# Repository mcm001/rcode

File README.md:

# rcode
stuff that doesn't belong anywhere else

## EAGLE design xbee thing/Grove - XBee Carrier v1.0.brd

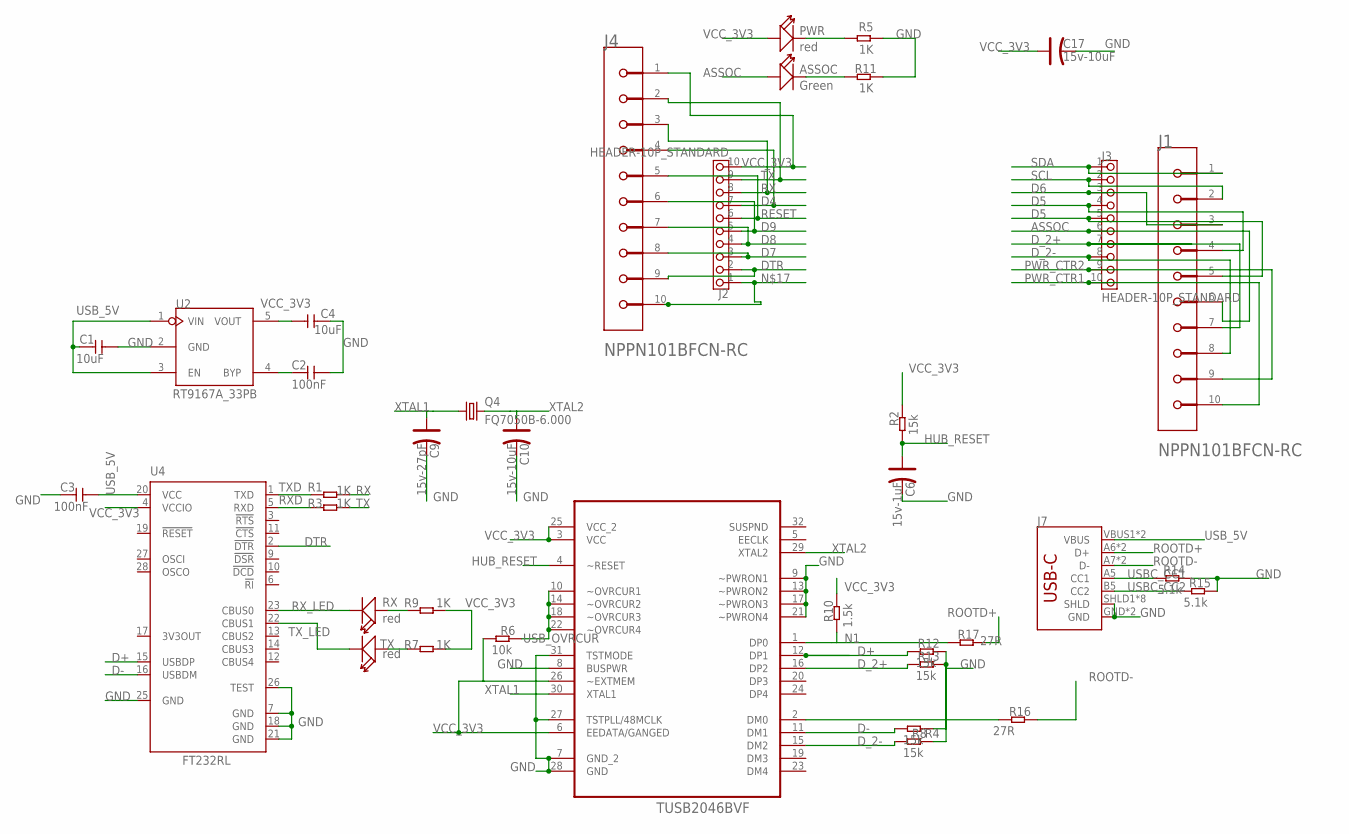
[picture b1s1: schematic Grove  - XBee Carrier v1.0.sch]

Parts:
ASSOC: Green; D0603
C1, C4: 10uF; 0805
C2, C3: 100nF; 0603
C6: 15v-1uF; AVX-A
C9: 15v-27pF; AVX-A
C10, C17: 15v-10uF; AVX-A
J1, J4: SULLINS_NPPN101BFCN-RCSULLINS_NPPN101BFCN-RC_0_0; SULLINS_NPPN101BFCN-RC_0
J2, J3: HEADER-10P_STANDARD; 2.54_10P
J7: USB_C2-LAYER; USB-C-16P
PWR: red; D0805
Q4: FQ7050B-6.000; FQ7050B
R1, R3, R5, R7, R9, R11: 1K; 0603
R2, R4, R8, R12, R13: 15k; 0603
R6: 10k; 0603
R10: 1.5k; 0603
R14, R15: 5.1k; 0603
R16, R17: 27R; 0603
RX: red; D0603
TX: red; D0603
U1: TUSB2046BVF; QFP80P900X900X145-32N
U2: RT9167A_33PB; SOT23-5
U4: FT232RL; SSOP28

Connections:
ASSOC: ASSOC.+, J1.6, J3.6
D4: J2.7, J4.4
D5: J1.4, J1.5, J3.4, J3.5
D6: J1.3, J3.3
D7: J2.3, J4.8
D8: J2.4, J4.7
D9: J2.5, J4.6
D+: R12.2, U1.12 (DP1), U4.15 (USBDP)
D-: R4.2, U1.11 (DM1), U4.16 (USBDM)
DTR: J2.2, J4.9, U4.2 (!DTR)
D_2+: J1.7, J3.7, R13.2, U1.16 (DP2)
D_2-: J1.8, J3.8, R8.2, U1.15 (DM2)
GND: C1.2, C2.2, C3.1, C4.2, C6.-, C9.-, C10.-, C17.-, J7.GND, J7.GND2 (GND), J7.SHLD1 (SHLD), J7.SHLD2 (SHLD), J7.SHLD3 (SHLD), J7.SHLD4 (SHLD), J7.SHLD5 (SHLD), J7.SHLD6 (SHLD), J7.SHLD7 (SHLD), J7.SHLD8 (SHLD), R4.1, R5.1, R8.1, R11.1, R12.1, R13.1, R14.1, R15.1, U1.7 (GND_2), U1.8 (BUSPWR), U1.9 (~PWRON1), U1.13 (~PWRON2), U1.17 (~PWRON3), U1.21 (~PWRON4), U1.27 (TSTPLL/48MCLK), U1.28 (GND), U1.31 (TSTMODE), U2.2 (GND), U4.7 (GND), U4.18 (GND), U4.21 (GND), U4.25 (GND), U4.26 (TEST)
HUB_RESET: C6.+, R2.2, U1.4 (~RESET)
N1: R10.2, R17.2, U1.1 (DP0)
unnamed: PWR.-, R5.2
unnamed: R16.2, U1.2 (DM0)
unnamed: C2.1, U2.4 (BYP)
unnamed: ASSOC.-, R11.2
unnamed: R9.1, RX.+
unnamed: R7.1, TX.+
unnamed: J2.1, J4.10
PWR_CTR1: J1.10, J3.10
PWR_CTR2: J1.9, J3.9
RESET: J2.6, J4.5
ROOTD+: J7.A6 (D+), J7.B6 (D+), R17.1
ROOTD-: J7.A7 (D-), J7.B7 (D-), R16.1
RX: J2.8, J4.3, R1.2
RXD: R3.1, U4.5 (RXD)
RX_LED: RX.-, U4.23 (CBUS0)
SCL: J1.2, J3.2
SDA: J1.1, J3.1
TX: J2.9, J4.2, R3.2
TXD: R1.1, U4.1 (TXD)
TX_LED: TX.-, U4.22 (CBUS1)
USBC_CC1: J7.A5 (CC1), R14.2
USBC_CC2: J7.B5 (CC2), R15.2
USB_5V: C1.1, C3.2, J7.VBUS1 (VBUS), J7.VBUS2 (VBUS), U2.1 (VIN), U2.3 (EN), U4.20 (VCC)
USB_OVRCUR: R6.1, U1.10 (~OVRCUR1), U1.14 (~OVRCUR2), U1.18 (~OVRCUR3), U1.22 (~OVRCUR4)
VCC_3V3: C4.1, C17.+, J2.10, J4.1, PWR.+, R2.1, R6.2, R7.2, R9.2, R10.1, U1.3 (VCC), U1.6 (EEDATA/GANGED), U1.25 (VCC_2), U1.26 (~EXTMEM), U2.5 (VOUT), U4.4 (VCCIO)
XTAL1: C9.+, Q4.1, U1.30 (XTAL1)
XTAL2: C10.+, Q4.4 (2), U1.29 (XTAL2)

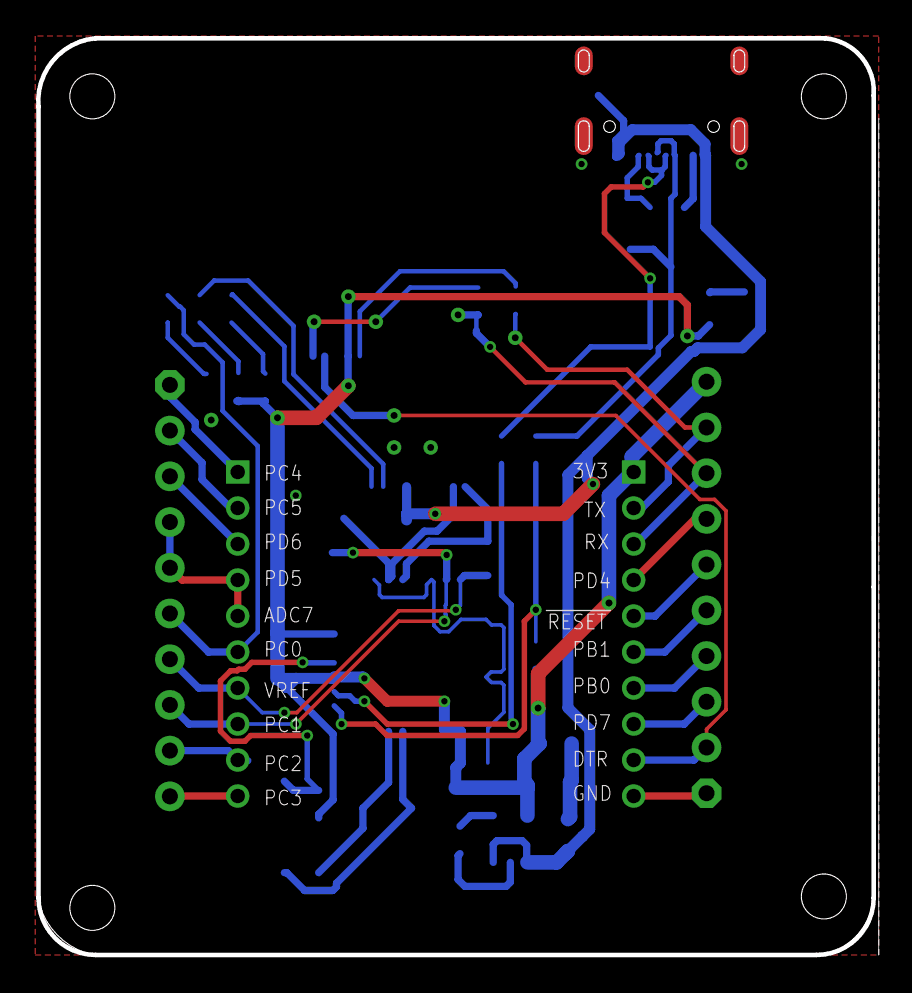
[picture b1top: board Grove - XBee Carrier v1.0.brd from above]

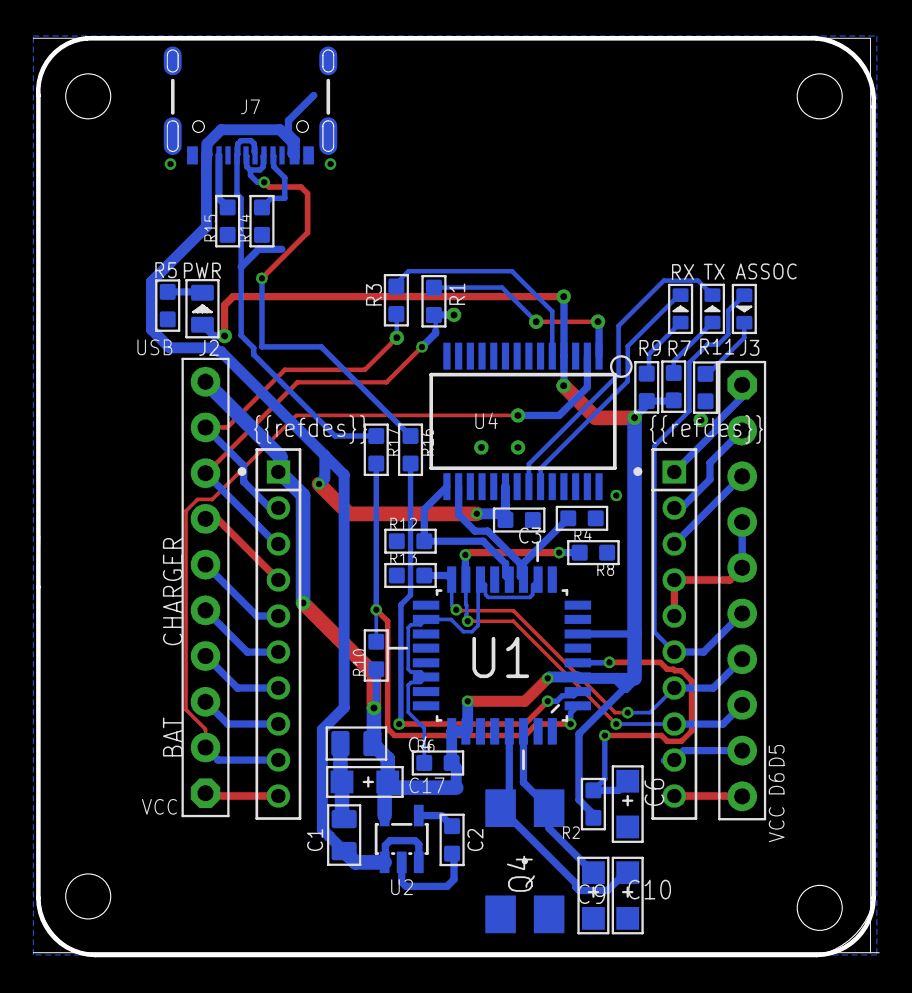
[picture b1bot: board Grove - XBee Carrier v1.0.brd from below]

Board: 2 copper layers, 46.4 x 50.9 mm, 38 parts (38 on the bottom side), 42 nets.

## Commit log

2018-11-14 added todo
2018-11-15 update todo
2018-11-25 added tensioner :D
2018-11-25 reorganization
2018-11-26 Updated to include pin retention
2018-11-26 fixed for no oled
2018-11-26 added arduino rcode
2018-11-26 fixed org
2018-11-26 banana2
2018-11-26 meme2
2018-11-26 Went and became the true fish
2018-11-27 added printer stuff
2018-11-27 meme
2018-11-27 alexisbad.jpg
2018-11-30 add endstop for z axis
2018-12-01 frc batt box stuff
2018-12-01 added nema 17 cad
2018-12-01 yeet
2018-12-01 mlem
2018-12-02 added mk3-ish
2018-12-06 update wifimd
2018-12-06 yay merge conflicts
2018-12-07 added port forwarding memes
2018-12-13 history notes yay
2018-12-22 added filament hanger hook thing
2018-12-31 owo quarter wave transforms broken
2019-01-07 reeeeee
2019-01-07 Add main grabber assem v2
2019-01-07 Moar shiv bois
2019-01-07 Add a ulna
2019-01-07 Full wrist assem
2019-01-07 Moar assem
2019-01-07 Add a yeet-o-vator
2019-01-07 More yeets for the elevator
2019-01-07 Add dimensioned drawings
2019-01-07 more yeetn't's
2019-01-24 weird
2019-01-24 add java stuff
2019-01-24 added gradle properties
2019-03-18 does this work?
2019-06-15 backup menu, printer config file
2019-06-23 i am actually confused but sure
2019-06-25 ZACH UR BAD
2019-06-25 zach ur still bad
2019-08-24 stuff
2019-08-24 Python bad
2019-08-28 yote
2019-08-29 screm usbc
2019-08-29 haha nou
2019-08-29 maybe impl'd hub, delet battery stuff
2019-08-29 Maybe fixed it
2019-08-30 haha yes
2019-08-30 plz dont break
2019-08-30 Maybe at least a little fix the things it's complaining about?
2019-08-30 add more resistors in series to Root D+ and D- pins
2019-08-31 make the ground plane actually a plane and not airwires
2019-08-31 yoink
2019-09-03 screm
2019-09-03 screm it works
2019-09-03 reeeeeeeeeename shit
2019-09-03 reeeelationship with sneklang ended
2019-09-04 Sneklang possibly gud
2019-09-09 eeee
2019-11-14 adsffsdaadfsfdsafds
2020-03-27 yeet the pendulum works
2020-03-27 Bump pillow from 5.2.0 to 6.2.0 in /python
    Bumps [pillow](https://github.com/python-pillow/Pillow) from 5.2.0 to 6.2.0.
    - [Release notes](https://github.com/python-pillow/Pillow/releases)
    - [Changelog](https://github.com/python-pillow/Pillow/blob/master/CHANGES.rst)
    - [Commits](https://github.com/python-pillow/Pillow/compare/5.2.0...6.2.0)
2020-03-27 Add velocity vector that follows the point around, document some stuff
2020-03-28 AAaaaaaah
2020-03-28 Add method to disable showing vector on point
2020-03-28 aaaaaaaaaah they're back
2020-03-30 Add white path following pendulum
2020-03-30 Technically hide the pendulum
2020-03-30 add multiple spirals (WIP), start cleaning up some odl code
2020-09-01 Add sonic buzz
2020-12-23 Bump pillow from 5.2.0 to 7.1.0 in /python
    Bumps [pillow](https://github.com/python-pillow/Pillow) from 5.2.0 to 7.1.0.
    - [Release notes](https://github.com/python-pillow/Pillow/releases)
    - [Changelog](https://github.com/python-pillow/Pillow/blob/master/CHANGES.rst)
    - [Commits](https://github.com/python-pillow/Pillow/compare/5.2.0...7.1.0)
2020-12-28 stuff?
2020-12-28 Add sonic cad
2021-03-19 Bump pillow from 5.2.0 to 8.1.1 in /python
    Bumps [pillow](https://github.com/python-pillow/Pillow) from 5.2.0 to 8.1.1.
    - [Release notes](https://github.com/python-pillow/Pillow/releases)
    - [Changelog](https://github.com/python-pillow/Pillow/blob/master/CHANGES.rst)
    - [Commits](https://github.com/python-pillow/Pillow/compare/5.2.0...8.1.1)
2021-04-05 Add altos
2021-06-08 Bump pillow from 5.2.0 to 8.2.0 in /python
    Bumps [pillow](https://github.com/python-pillow/Pillow) from 5.2.0 to 8.2.0.
    - [Release notes](https://github.com/python-pillow/Pillow/releases)
    - [Changelog](https://github.com/python-pillow/Pillow/blob/master/CHANGES.rst)
    - [Commits](https://github.com/python-pillow/Pillow/compare/5.2.0...8.2.0)
    ---
    updated-dependencies:
2021-08-21 eggfinder memes
2021-09-08 Bump pillow from 5.2.0 to 8.3.2 in /python
    Bumps [pillow](https://github.com/python-pillow/Pillow) from 5.2.0 to 8.3.2.
    - [Release notes](https://github.com/python-pillow/Pillow/releases)
    - [Changelog](https://github.com/python-pillow/Pillow/blob/master/CHANGES.rst)
    - [Commits](https://github.com/python-pillow/Pillow/compare/5.2.0...8.3.2)
    ---
    updated-dependencies:
2021-09-20 Add eggfinder groundstation
2021-09-20 Refactor GPS
2021-09-20 Add random python stuff
2021-09-29 Fix serial
2021-10-12 Bump opencv-python from 3.4.2.17 to 3.4.7.28 in /python
    Bumps [opencv-python](https://github.com/skvark/opencv-python) from 3.4.2.17 to 3.4.7.28.
    - [Release notes](https://github.com/skvark/opencv-python/releases)
    - [Commits](https://github.com/skvark/opencv-python/commits)
    ---
    updated-dependencies:
    - dependency-name: opencv-python
2021-10-12 Bump opencv-python from 3.4.2.17 to 4.2.0.32 in /python
    Bumps [opencv-python](https://github.com/skvark/opencv-python) from 3.4.2.17 to 4.2.0.32.
    - [Release notes](https://github.com/skvark/opencv-python/releases)
    - [Commits](https://github.com/skvark/opencv-python/commits)
    ---
    updated-dependencies:
    - dependency-name: opencv-python
2021-10-22 Random matlab stuff
2021-12-12 Switch to 3-state KF
    Fix errors
2021-12-26 Move stuff
2021-12-27 Make three.js work
2021-12-27 Add python start note
2021-12-27 add another light, fix compliation error
2022-01-13 Bump pillow from 5.2.0 to 9.0.0 in /python
    Bumps [pillow](https://github.com/python-pillow/Pillow) from 5.2.0 to 9.0.0.
    - [Release notes](https://github.com/python-pillow/Pillow/releases)
    - [Changelog](https://github.com/python-pillow/Pillow/blob/main/CHANGES.rst)
    - [Commits](https://github.com/python-pillow/Pillow/compare/5.2.0...9.0.0)
    ---
    updated-dependencies:
2022-03-12 Bump pillow from 5.2.0 to 9.0.1 in /python
    Bumps [pillow](https://github.com/python-pillow/Pillow) from 5.2.0 to 9.0.1.
    - [Release notes](https://github.com/python-pillow/Pillow/releases)
    - [Changelog](https://github.com/python-pillow/Pillow/blob/main/CHANGES.rst)
    - [Commits](https://github.com/python-pillow/Pillow/compare/5.2.0...9.0.1)
    ---
    updated-dependencies:
2022-04-25 Various memes
2022-06-22 Bump numpy from 1.15.0 to 1.22.0 in /python
    Bumps [numpy](https://github.com/numpy/numpy) from 1.15.0 to 1.22.0.
    - [Release notes](https://github.com/numpy/numpy/releases)
    - [Changelog](https://github.com/numpy/numpy/blob/main/doc/HOWTO_RELEASE.rst)
    - [Commits](https://github.com/numpy/numpy/compare/v1.15.0...v1.22.0)
    ---
    updated-dependencies:
2022-08-03 Misc graphs
2022-11-22 Bump pillow from 5.2.0 to 9.3.0 in /python
    Bumps [pillow](https://github.com/python-pillow/Pillow) from 5.2.0 to 9.3.0.
    - [Release notes](https://github.com/python-pillow/Pillow/releases)
    - [Changelog](https://github.com/python-pillow/Pillow/blob/main/CHANGES.rst)
    - [Commits](https://github.com/python-pillow/Pillow/compare/5.2.0...9.3.0)
    ---
    updated-dependencies:
2023-07-06 Bump scipy from 1.1.0 to 1.10.0 in /python
    Bumps [scipy](https://github.com/scipy/scipy) from 1.1.0 to 1.10.0.
    - [Release notes](https://github.com/scipy/scipy/releases)
    - [Commits](https://github.com/scipy/scipy/compare/v1.1.0...v1.10.0)
    ---
    updated-dependencies:
    - dependency-name: scipy
2023-10-03 Bump pillow from 5.2.0 to 10.0.1 in /python
    Bumps [pillow](https://github.com/python-pillow/Pillow) from 5.2.0 to 10.0.1.
    - [Release notes](https://github.com/python-pillow/Pillow/releases)
    - [Changelog](https://github.com/python-pillow/Pillow/blob/main/CHANGES.rst)
    - [Commits](https://github.com/python-pillow/Pillow/compare/5.2.0...10.0.1)
    ---
    updated-dependencies:
2024-10-02 Initial commit of pi pico code
2024-10-02 mebbe?
2024-11-10 Add windvane-pico
2024-12-27 exif editor

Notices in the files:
parts and their libraries:
SparkFun-Connectors: Licensing: Creative Commons ShareAlike 4.0 International - https://creativecommons.org/licenses/by-sa/4.0
